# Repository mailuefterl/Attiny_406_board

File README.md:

# Attiny_406_board
Attiny 406 breakout board

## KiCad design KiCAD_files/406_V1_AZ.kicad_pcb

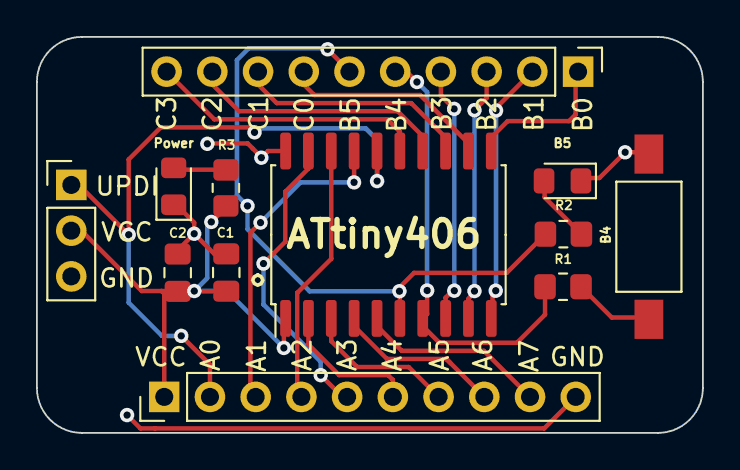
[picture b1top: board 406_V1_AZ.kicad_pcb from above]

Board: 2 copper layers, 37.0 x 22.0 mm, 12 parts (0 on the bottom side), 23 nets.

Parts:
B4: SW_Push; SW_SPST_FSMSM
B5: LED Rt; LED_0805_2012Metric_Pad1.15x1.40mm_HandSolder
C1: 0.1uF; C_0805_2012Metric_Pad1.18x1.45mm_HandSolder
C2: 2.2uF; C_0805_2012Metric_Pad1.18x1.45mm_HandSolder
J1, J3: Conn_01x10_Male; PinHeader_1x10_P2.54mm_Vertical
J2: Conn_01x03_Male; PinHeader_1x03_P2.54mm_Vertical
Power: LED GN; LED_0805_2012Metric_Pad1.15x1.40mm_HandSolder
R1, R2, R3: 1K; R_0805_2012Metric_Pad1.20x1.40mm_HandSolder
U1: ATtiny406-S; SOIC-20W_7.5x12.8mm_P1.27mm

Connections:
GND: B4.2, B5.1 (K), C1.2, C2.2, J1.10, J2.3, Power.1 (K), U1.20 (GND)
unnamed: B5.2 (A), R2.2
unnamed: Power.2 (A), R3.2
unnamed: B4.1, R1.2
PA0: J1.2, J2.1, U1.16 (~RESET/PA0)
PA1: J1.3, U1.17 (PA1)
PA2: J1.4, U1.18 (PA2)
PA3: J1.5, U1.19 (PA3)
PA4: J1.6, U1.2 (PA4)
PA5: J1.7, U1.3 (PA5)
PA6: J1.8, U1.4 (PA6)
PA7: J1.9, U1.5 (PA7)
PB0: J3.1, U1.11 (PB0)
PB1: J3.2, U1.10 (PB1)
PB2: J3.3, U1.9 (PB2)
PB3: J3.4, U1.8 (PB3)
PB4: J3.5, R1.1, U1.7 (PB4)
PB5: J3.6, R2.1, U1.6 (PB5)
PC0: J3.7, U1.12 (PC0)
PC1: J3.8, U1.13 (PC1)
PC2: J3.9, U1.14 (PC2)
PC3: J3.10, U1.15 (PC3)
VCC: C1.1, C2.1, J1.1, J2.2, R3.1, U1.1 (VCC)
